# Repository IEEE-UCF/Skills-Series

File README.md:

# IEEE-UCF-Skills-Series
Repository for IEEE UCF's skills series. Current Skills series to date:
1. Version control with Github
2. Digital Audio Workstations (DAWs)
3. Basics of Verilog and RTL design
4. PCB design with KiCAD
5. Embedded programming with MSP430
6. RISC-V single-cycle processor design

Future/planned skills series
1. UI/UX design
2. DAW MK2.0

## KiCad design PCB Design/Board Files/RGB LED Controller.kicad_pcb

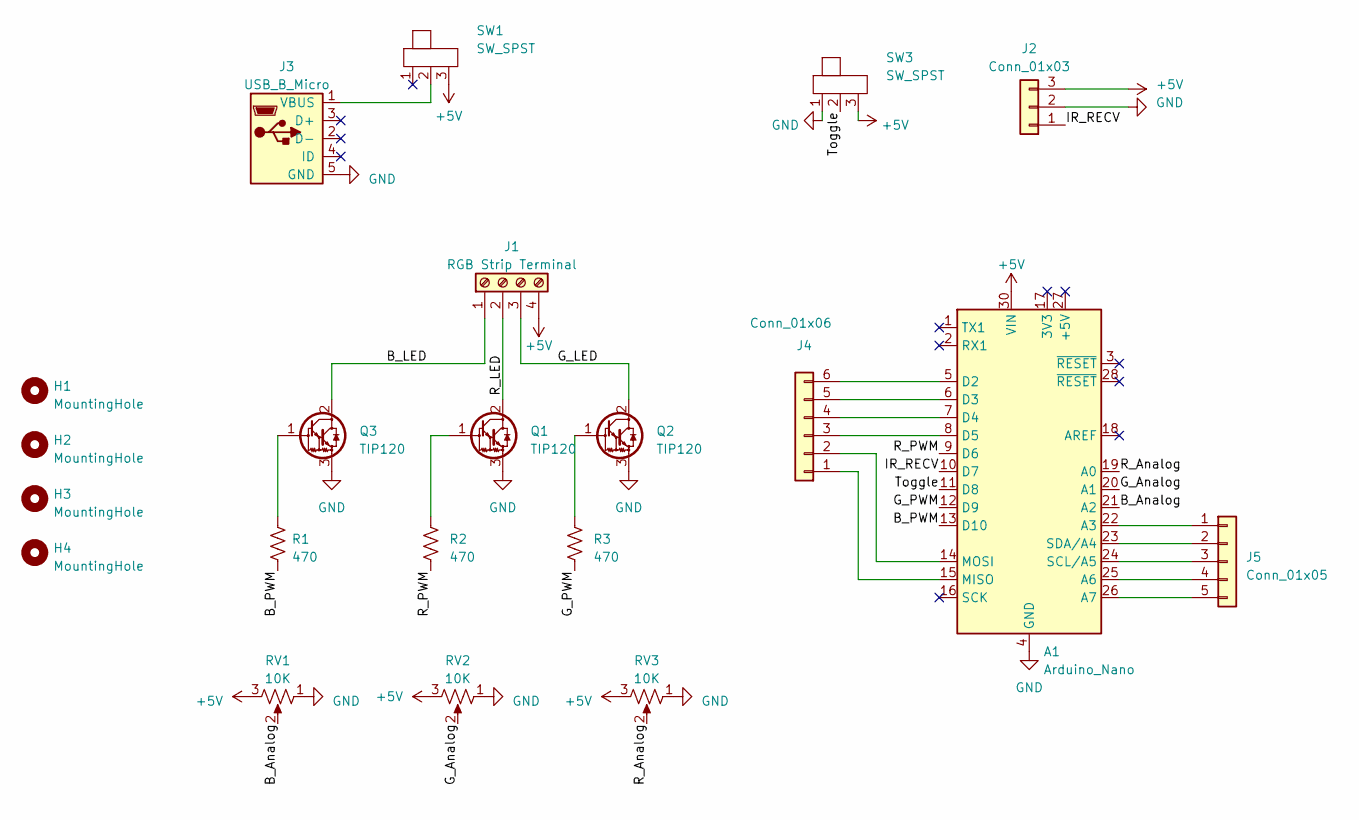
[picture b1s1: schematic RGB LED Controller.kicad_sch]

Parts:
A1: Arduino_Nano
H1, H2, H3, H4: MountingHole; MountingHole_3.2mm_M3
J1: RGB Strip Terminal; LED Strip Terminal Block
J2: Conn_01x03; PinHeader_1x03_P2.54mm_Vertical
J3: USB_B_Micro; MicroUSB Port
J4: Conn_01x06; PinHeader_1x06_P2.54mm_Vertical
J5: Conn_01x05; PinHeader_1x05_P2.54mm_Vertical
Q1, Q2, Q3: TIP120; TO-220-3_Vertical
R1, R2, R3: 470; R_Axial_DIN0207_L6.3mm_D2.5mm_P7.62mm_Horizontal
RV1, RV2, RV3: 10K; 10K Potentiometer Dial
SW1, SW3: SW_SPST; Slide Switch

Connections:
+5V: A1.30 (VIN), J1.4, J2.3, RV1.3, RV2.3, RV3.3, SW1.3, SW3.3
/B_Analog: A1.21 (A2), RV1.2
/B_LED: J1.1, Q3.2 (C)
/B_PWM: A1.13 (D10), R1.1
/G_Analog: A1.20 (A1), RV2.2
/G_LED: J1.3, Q2.2 (C)
/G_PWM: A1.12 (D9), R3.1
/IR_RECV: A1.10 (D7), J2.1
/R_Analog: A1.19 (A0), RV3.2
/R_LED: J1.2, Q1.2 (C)
/R_PWM: A1.9 (D6), R2.1
/Toggle: A1.11 (D8), SW3.2
GND: A1.4 (GND), A1.29 (GND), J2.2, J3.5 (GND), Q1.3 (E), Q2.3 (E), Q3.3 (E), RV1.1, RV2.1, RV3.1, SW3.1
unnamed: A1.22 (A3), J5.1
unnamed: A1.25 (A6), J5.4
unnamed: A1.26 (A7), J5.5
unnamed: A1.5 (D2), J4.6
unnamed: A1.6 (D3), J4.5
unnamed: A1.7 (D4), J4.4
unnamed: A1.8 (D5), J4.3
unnamed: A1.15 (MISO), J4.1
unnamed: A1.14 (MOSI), J4.2
unnamed: A1.24 (SCL/A5), J5.3
unnamed: A1.23 (SDA/A4), J5.2
unnamed: J3.1 (VBUS), SW1.2
unnamed: Q1.1 (B), R2.2
unnamed: Q2.1 (B), R3.2
unnamed: Q3.1 (B), R1.2

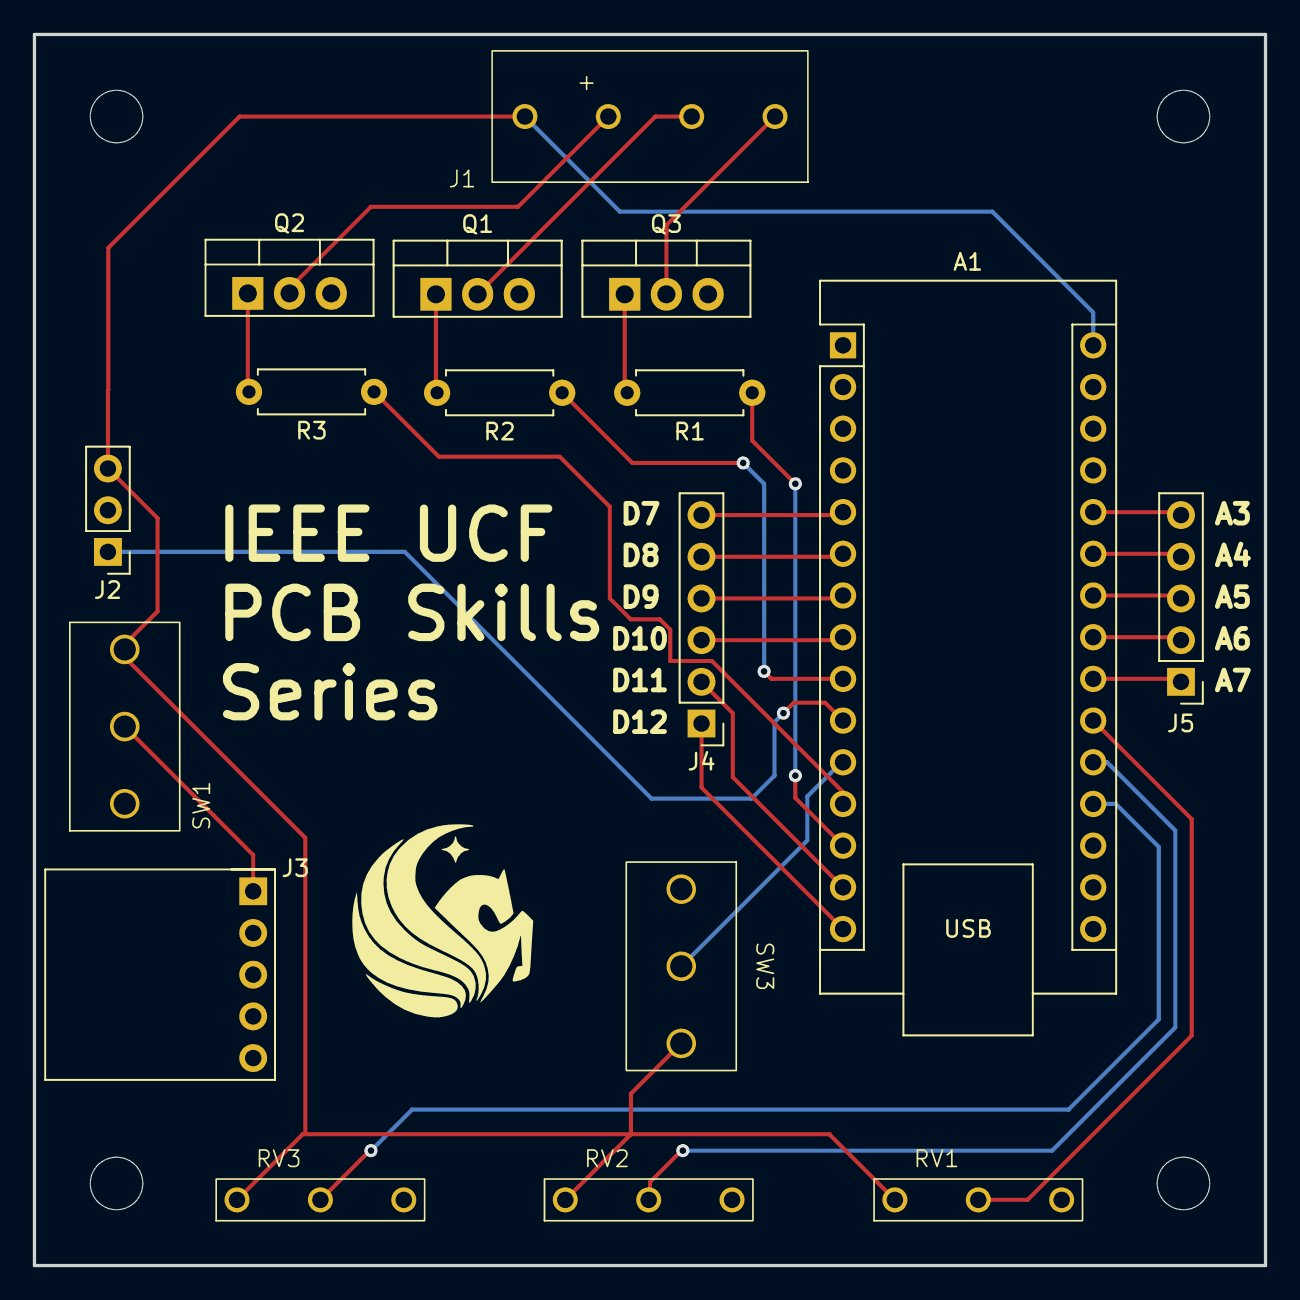
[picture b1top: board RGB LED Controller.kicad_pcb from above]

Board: 2 copper layers, 75.0 x 75.0 mm, 21 parts (0 on the bottom side), 28 nets.

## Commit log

2024-02-17 added git ss pressy
2024-07-16 workshops 1 & 2
